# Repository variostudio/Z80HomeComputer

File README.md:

# Z80HomeComputer
Simple and easy to build Z80 based computer

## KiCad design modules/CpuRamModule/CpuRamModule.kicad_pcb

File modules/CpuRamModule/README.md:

## CPU and RAM module
Base module contains Z80 CPU and banked RAM

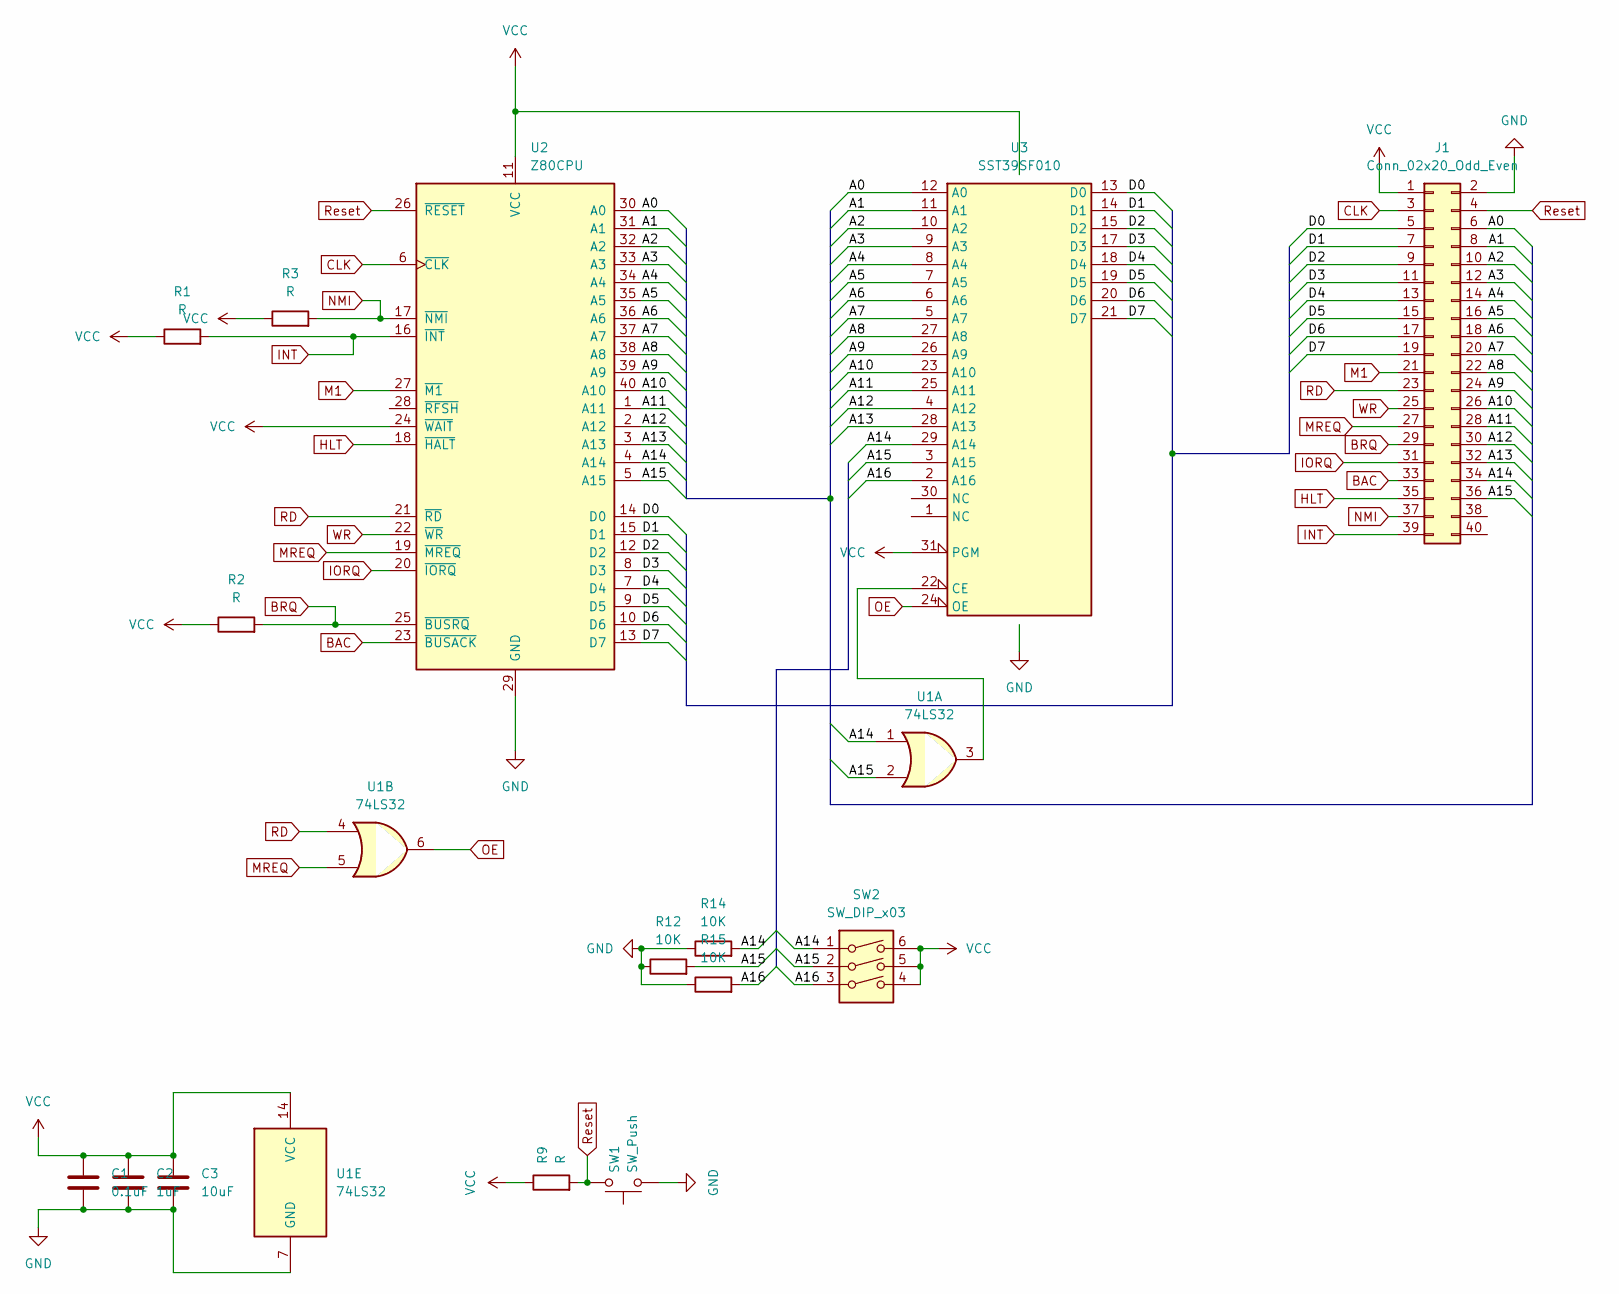
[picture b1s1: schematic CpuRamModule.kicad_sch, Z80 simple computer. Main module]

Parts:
C1: 0.1uF; C_Rect_L4.0mm_W2.5mm_P2.50mm
C2: 1uF; C_Rect_L4.0mm_W2.5mm_P2.50mm
C3: 10uF; C_Rect_L4.0mm_W2.5mm_P2.50mm
J1: Conn_02x20_Odd_Even; PinHeader_2x20_P2.54mm_Vertical
R1, R2, R3, R9: R; R_Axial_DIN0204_L3.6mm_D1.6mm_P7.62mm_Horizontal
R12, R14, R15: 10K; R_Axial_DIN0204_L3.6mm_D1.6mm_P7.62mm_Horizontal
SW1: SW_Push; SW_PUSH_6mm
SW2: SW_DIP_x03; SW_DIP_SPSTx03_Slide_9.78x9.8mm_W7.62mm_P2.54mm
U1: 74LS32; DIP-14_W7.62mm_Socket
U2: Z80CPU; DIP-40_W15.24mm_Socket
U3: SST39SF010; DIP-32_W15.24mm_Socket

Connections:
/A0: J1.6, U2.30 (A0), U3.12 (A0)
/A1: J1.8, U2.31 (A1), U3.11 (A1)
/A2: J1.10, U2.32 (A2), U3.10 (A2)
/A3: J1.12, U2.33 (A3), U3.9 (A3)
/A4: J1.14, U2.34 (A4), U3.8 (A4)
/A5: J1.16, U2.35 (A5), U3.7 (A5)
/A6: J1.18, U2.36 (A6), U3.6 (A6)
/A7: J1.20, U2.37 (A7), U3.5 (A7)
/A8: J1.22, U2.38 (A8), U3.27 (A8)
/A9: J1.24, U2.39 (A9), U3.26 (A9)
/A10: J1.26, U2.40 (A10), U3.23 (A10)
/A11: J1.28, U2.1 (A11), U3.25 (A11)
/A12: J1.30, U2.2 (A12), U3.4 (A12)
/A13: J1.32, U2.3 (A13), U3.28 (A13)
/A14: J1.34, R14.2, SW2.1, U1.1, U2.4 (A14), U3.29 (A14)
/A15: J1.36, R12.2, SW2.2, U1.2, U2.5 (A15), U3.3 (A15)
/A16: R15.2, SW2.3, U3.2 (A16)
/D0: J1.5, U2.14 (D0), U3.13 (D0)
/D1: J1.7, U2.15 (D1), U3.14 (D1)
/D2: J1.9, U2.12 (D2), U3.15 (D2)
/D3: J1.11, U2.8 (D3), U3.17 (D3)
/D4: J1.13, U2.7 (D4), U3.18 (D4)
/D5: J1.15, U2.9 (D5), U3.19 (D5)
/D6: J1.17, U2.10 (D6), U3.20 (D6)
/D7: J1.19, U2.13 (D7), U3.21 (D7)
BAC: J1.33, U2.23 (~BUSACK)
BRQ: J1.29, R2.2, U2.25 (~BUSRQ)
CLK: J1.3, U2.6 (~CLK)
GND: C1.2, C2.2, C3.2, J1.2, R12.1, R14.1, R15.1, SW1.1, U1.7 (GND), U2.29 (GND), U3.16 (GND)
HLT: J1.35, U2.18 (~HALT)
INT: J1.39, R1.2, U2.16 (~INT)
IORQ: J1.31, U2.20 (~IORQ)
M1: J1.21, U2.27 (~M1)
MREQ: J1.27, U1.5, U2.19 (~MREQ)
NMI: J1.37, R3.2, U2.17 (~NMI)
unnamed: U1.3, U3.22 (CE)
OE: U1.6, U3.24 (OE)
RD: J1.23, U1.4, U2.21 (~RD)
Reset: J1.4, R9.2, SW1.2, U2.26 (~RESET)
VCC: C1.1, C2.1, C3.1, J1.1, R1.1, R2.1, R3.1, R9.1, SW2.4, SW2.5, SW2.6, U1.14 (VCC), U2.11 (VCC), U2.24 (~WAIT), U3.31 (PGM), U3.32 (VCC)
WR: J1.25, U2.22 (~WR)

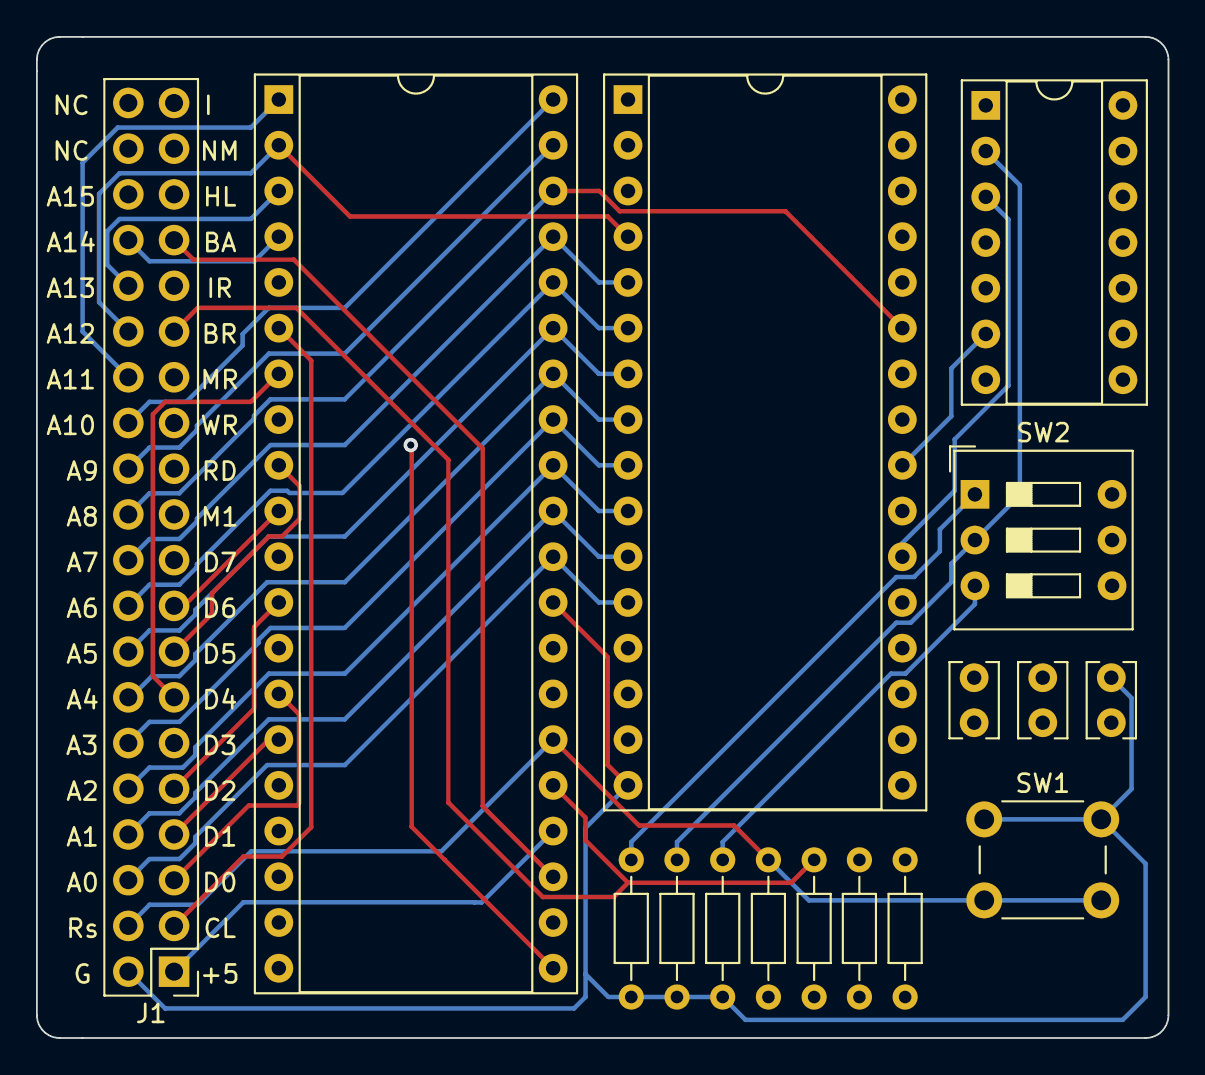
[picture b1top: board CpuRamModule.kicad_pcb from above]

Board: 4 copper layers, 62.9 x 55.6 mm, 16 parts (0 on the bottom side), 41 nets.

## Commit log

2022-11-27 CPU and RAM module added
2022-12-01 Final before order
2022-12-01 Schematics
2022-12-01 Docs and READMe's added
